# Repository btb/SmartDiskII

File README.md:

# SmartDiskII

The SmartDiskII is basically an Apple "Liron" disk controller with the IWM chip
replaced by the discrete components from the Disk II controller, which
the IWM was originally based on, and using firmware (i.e. SoftSP) which
has been appropriately modified to use those components instead of the IWM.

[Interactive BOM](https://btb.github.io/SmartDiskII/bom/SmartDiskII.html)

## SmartPort Operation

Because the SoftSP firmware (as of v6) is slot-dependent, a different copy is
required for each slot the card may be used in. The slot 1 version is in the 1xxx
region of the EPROM, slot 2 version is at 2xxx, etc.
A set of latches (U9) is used to automatically select the appropriate region
depending on which slot the SmartDiskII is placed in.

## Disk II Operation (experimental)

The card is designed to also work as a regular Disk II controller, though 
results can be inconsistent depending on the components used. Failures of 
this system can lead to corrupted floppy disks.

For this reason it is recommended to use true TTL ICs for all of the logic 
chips. In addition, for the chip at U5, Apple's original Disk II 
controller design called for a 9334 rather than a 74LS259. Indeed, using a 
9334 does appear to make the circuit more tolerant of these issues.  

5.25 Floppy operation works by having the Disk II boot rom in the 0xxx
region of the EPROM, and therefore active while U9 is held in
reset. Plugging a floppy drive into the DRV1 connector should automatically
activate the correct firmware because of the presence of +5V on pin 12, but
because some devices do not have that pin connected,
you can also close jumper JP8 to force the card into Disk II boot mode.

## Configuration

U8 is the standard [16-sector Disk II state machine data, P6](firmware/341-0128_P6A.bin), on a 2716-compatible EPROM.

U11 is a special combination of the Disk II boot ROM and the SoftSP firmware, [SmartDiskII.bin](firmware/SmartDiskII.bin).

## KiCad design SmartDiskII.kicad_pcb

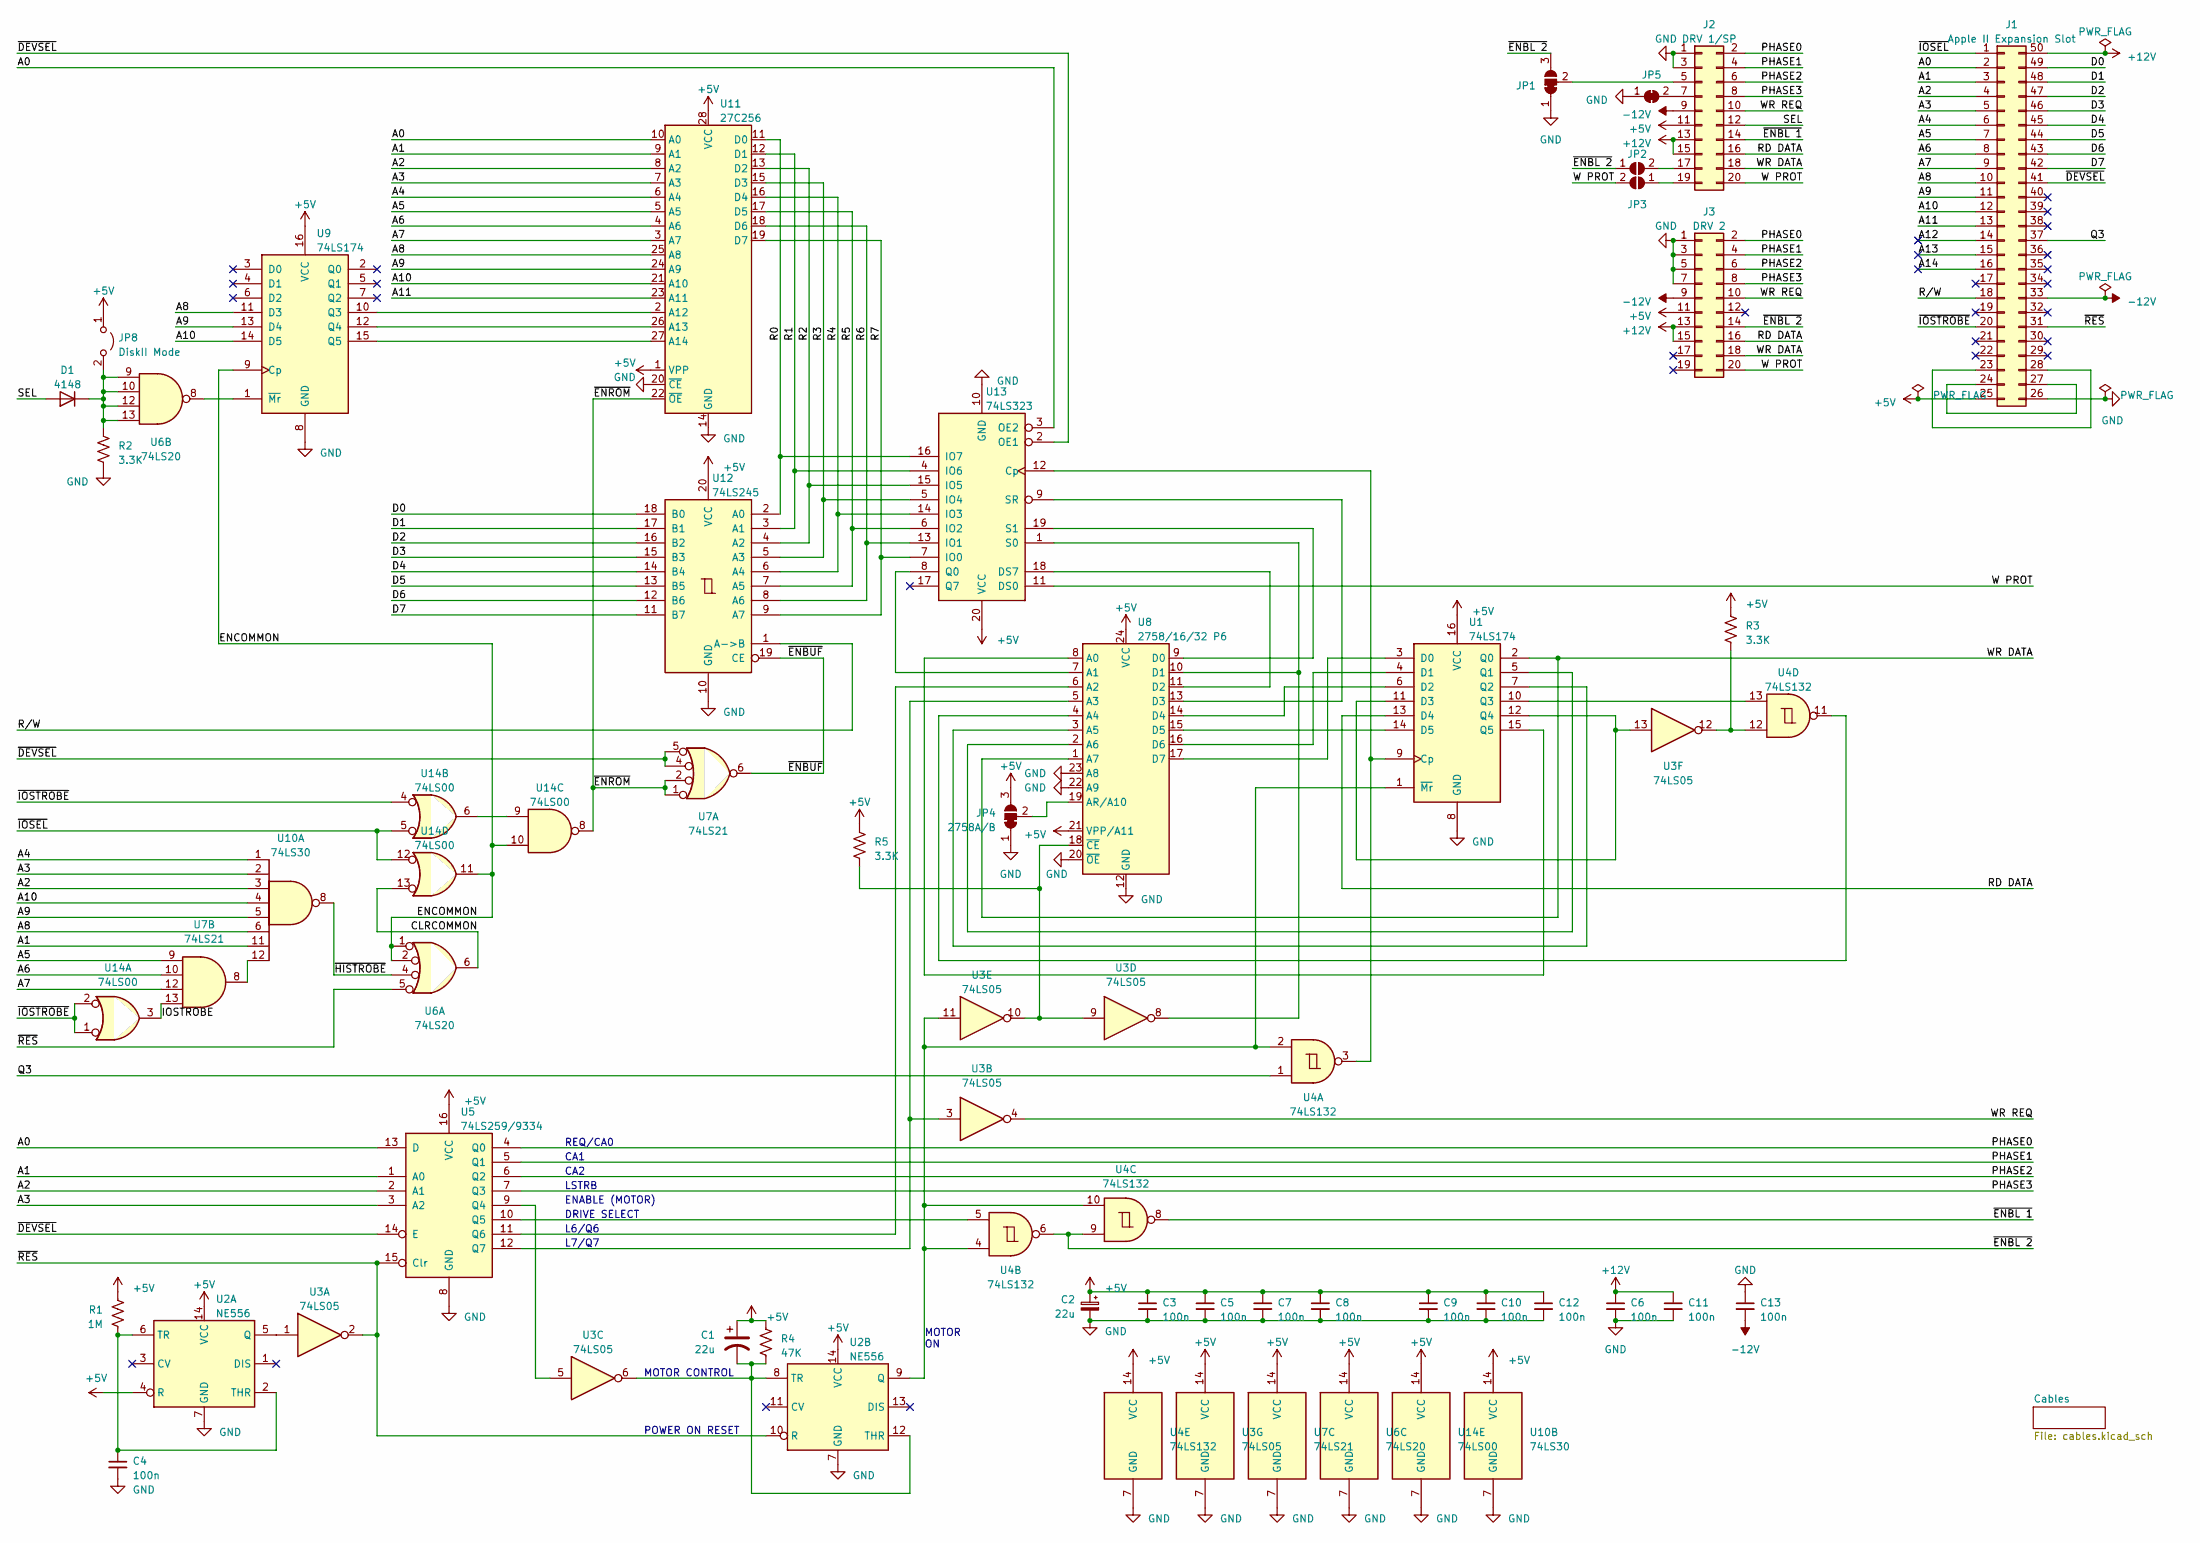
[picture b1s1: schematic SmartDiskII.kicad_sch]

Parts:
C1, C2: 22u; CP_Radial_D5.0mm_P2.50mm
C3, C4, C5, C6, C7, C8, C9, C10, C11, C12, C13: 100n; C_Disc_D4.3mm_W1.9mm_P5.00mm
D1: 4148; D_DO-35_SOD27_P7.62mm_Horizontal
J1: Apple II Expansion Slot; Apple II Expansion Edge Connector
J2: DRV 1/SP; PinHeader_2x10_P2.54mm_Vertical_Shrouded
J3: DRV 2; PinHeader_2x10_P2.54mm_Vertical_Shrouded
JP1: SolderJumper-3_P1.3mm_Bridged12_RoundedPad1.0x1.5mm_NumberL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
JP2, JP3: SolderJumper-2_P1.3mm_Open_RoundedPad1.0x1.5mm
JP4: 2758A/B; SolderJumper-3_P1.3mm_Bridged12_RoundedPad1.0x1.5mm_NumberL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
JP5: SolderJumper-2_P1.3mm_Bridged_RoundedPad1.0x1.5mm
JP8: DiskII Mode; PinHeader_1x02_P2.54mm_Vertical
R1: 1M; R_Axial_DIN0207_L6.3mm_D2.5mm_P10.16mm_Horizontal
R2, R3, R5: 3.3K; R_Axial_DIN0207_L6.3mm_D2.5mm_P10.16mm_Horizontal
R4: 47K; R_Axial_DIN0207_L6.3mm_D2.5mm_P10.16mm_Horizontal
U1, U9: 74LS174; DIP-16_W7.62mm
U2: NE556; DIP-14_W7.62mm
U3: 74LS05; DIP-14_W7.62mm
U4: 74LS132; DIP-14_W7.62mm
U5: 74LS259/9334; DIP-16_W7.62mm
U6: 74LS20; DIP-14_W7.62mm
U7: 74LS21; DIP-14_W7.62mm
U8: 2758/16/32 P6; DIP-24_W15.24mm
U10: 74LS30; DIP-14_W7.62mm
U11: 27C256; DIP-28_W15.24mm
U12: 74LS245; DIP-20_W7.62mm
U13: 74LS323; DIP-20_W7.62mm
U14: 74LS00; DIP-14_W7.62mm

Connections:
+5V: C1.1, C2.1, C3.1, C5.1, C7.1, C8.1, C9.1, C10.1, C12.1, J1.25, J2.11, J3.11, JP4.3 (B), JP8.1 (A), R1.1, R3.1, R4.2, R5.1, U1.16 (VCC), U2.4 (R), U2.14 (VCC), U3.14 (VCC), U4.14 (VCC), U5.16 (VCC), U6.14 (VCC), U7.14 (VCC), U8.21 (VPP/A11), U8.24 (VCC), U9.16 (VCC), U10.14 (VCC), U11.1 (VPP), U11.28 (VCC), U12.20 (VCC), U13.20 (VCC), U14.14 (VCC)
+12V: C6.1, C11.1, J1.50, J2.13, J2.15, J3.13, J3.15
-12V: C13.2, J1.33, J2.9, J3.9
/A0: J1.2, U5.13 (D), U11.10 (A0), U13.3 (OE2)
/A1: J1.3, U5.1 (A0), U10.11, U11.9 (A1)
/A2: J1.4, U5.2 (A1), U10.3, U11.8 (A2)
/A3: J1.5, U5.3 (A2), U10.2, U11.7 (A3)
/A4: J1.6, U10.1, U11.6 (A4)
/A5: J1.7, U7.9, U11.5 (A5)
/A6: J1.8, U7.10, U11.4 (A6)
/A7: J1.9, U7.12, U11.3 (A7)
/A8: J1.10, U9.11 (D3), U10.6, U11.25 (A8)
/A9: J1.11, U9.13 (D4), U10.5, U11.24 (A9)
/A10: J1.12, U9.14 (D5), U10.4, U11.21 (A10)
/A11: J1.13, U11.23 (A11)
/A12: J1.14
/A13: J1.15
/A14: J1.16
/CLRCOMMON: U6.6, U14.13
/D0: J1.49, U12.18 (B0)
/D1: J1.48, U12.17 (B1)
/D2: J1.47, U12.16 (B2)
/D3: J1.46, U12.15 (B3)
/D4: J1.45, U12.14 (B4)
/D5: J1.44, U12.13 (B5)
/D6: J1.43, U12.12 (B6)
/D7: J1.42, U12.11 (B7)
/ENCOMMON: U6.1, U6.2, U9.9 (Cp), U14.10, U14.11
/IOSTROBE: U7.13, U14.3
/PHASE0: J2.2, J3.2, U5.4 (Q0)
/PHASE1: J2.4, J3.4, U5.5 (Q1)
/PHASE2: J2.6, J3.6, U5.6 (Q2)
/PHASE3: J2.8, J3.8, U5.7 (Q3)
/Q3: J1.37, U4.1
/R0: U11.11 (D0), U12.2 (A0), U13.16 (IO7)
/R1: U11.12 (D1), U12.3 (A1), U13.4 (IO6)
/R2: U11.13 (D2), U12.4 (A2), U13.15 (IO5)
/R3: U11.15 (D3), U12.5 (A3), U13.5 (IO4)
/R4: U11.16 (D4), U12.6 (A4), U13.14 (IO3)
/R5: U11.17 (D5), U12.7 (A5), U13.6 (IO2)
/R6: U11.18 (D6), U12.8 (A6), U13.13 (IO1)
/R7: U11.19 (D7), U12.9 (A7), U13.7 (IO0)
/RD DATA: J2.16, J3.16, U1.13 (D4)
/R/W: J1.18, U12.1 (A->B)
/SEL: D1.2 (A), J2.12
/W PROT: J2.20, J3.20, JP3.2 (B), U13.11 (DS0)
/WR DATA: J2.18, J3.18, U1.2 (Q0), U8.1 (A7)
/WR REQ: J2.10, J3.10, U3.4
/~DEVSEL: J1.41, U5.14 (E), U7.4, U7.5, U13.2 (OE1)
/~ENBL 1: J2.14, U4.8
/~ENBL 2: J3.14, JP1.3 (B), JP2.1 (A), U4.6, U4.9
/~ENBUF: U7.6, U12.19 (CE)
/~ENROM: U7.1, U7.2, U11.22 (~OE), U14.8
/~HISTROBE: U6.4, U10.8
/~IOSEL: J1.1, U14.5, U14.12
/~IOSTROBE: J1.20, U14.1, U14.2, U14.4
/~RES: J1.31, U2.10 (R), U3.2, U5.15 (Clr), U6.5
GND: C2.2, C3.2, C4.2, C5.2, C6.2, C7.2, C8.2, C9.2, C10.2, C11.2, C12.2, C13.1, J1.26, J2.1, J2.3, J3.1, J3.3, J3.5, J3.7, JP1.1 (A), JP4.1 (A), JP5.1 (A), R2.2, U1.8 (GND), U2.7 (GND), U3.7 (GND), U4.7 (GND), U5.8 (GND), U6.7 (GND), U7.7 (GND), U8.12 (GND), U8.20 (~OE), U8.22 (A9), U8.23 (A8), U9.8 (GND), U10.7 (GND), U11.14 (GND), U11.20 (~CE), U12.10 (GND), U13.10 (GND), U14.7 (GND)
unnamed: D1.1 (K), JP8.2 (B), R2.1, U6.9, U6.10, U6.12, U6.13
unnamed: J1.23, J1.28
unnamed: J1.24, J1.27
unnamed: J2.5, JP1.2 (C)
unnamed: J2.7, JP5.2 (B)
unnamed: J2.17, JP2.2 (B)
unnamed: J2.19, JP3.1 (A)
unnamed: JP4.2 (C), U8.19 (AR/A10)
unnamed: R3.2, U3.12, U4.12
unnamed: U1.9 (Cp), U4.3, U13.12 (Cp)
unnamed: U1.3 (D0), U8.17 (D7)
unnamed: U1.4 (D1), U8.16 (D6)
unnamed: U1.6 (D2), U8.14 (D4)
unnamed: U1.11 (D3), U1.12 (Q4), U3.13
unnamed: U1.14 (D5), U8.15 (D5)
unnamed: U1.5 (Q1), U8.2 (A6)
unnamed: U1.7 (Q2), U8.3 (A5)
unnamed: U1.10 (Q3), U4.13
unnamed: U1.15 (Q5), U8.8 (A0)
unnamed: U1.1 (~Mr), U2.9 (Q), U3.11, U4.2, U4.4, U4.10
unnamed: U2.5 (Q), U3.1
unnamed: C4.1, R1.2, U2.2 (THR), U2.6 (TR)
unnamed: C1.2, R4.1, U2.8 (TR), U2.12 (THR), U3.6
unnamed: U3.5, U5.9 (Q4)
unnamed: U4.5, U5.10 (Q5)
unnamed: U5.11 (Q6), U8.6 (A2)
unnamed: U3.3, U5.12 (Q7), U8.5 (A3)
unnamed: U4.11, U8.4 (A4)
unnamed: R5.2, U3.9, U3.10, U8.18 (~CE)
unnamed: U6.8, U9.1 (~Mr)
unnamed: U7.8, U10.12
unnamed: U9.10 (Q3), U11.2 (A12)
unnamed: U9.12 (Q4), U11.26 (A13)
unnamed: U9.15 (Q5), U11.27 (A14)
unnamed: U8.11 (D2), U13.18 (DS7)
unnamed: U8.7 (A1), U13.8 (Q0)
unnamed: U3.8, U8.10 (D1), U13.1 (S0)
unnamed: U8.9 (D0), U13.19 (S1)
unnamed: U8.13 (D3), U13.9 (SR)
unnamed: U14.6, U14.9

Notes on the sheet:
MOTOR ON
CA2
REQ/CA0
POWER ON RESET
ENABLE (MOTOR)
L7/Q7
DRIVE SELECT
MOTOR CONTROL
L6/Q6
CA1
LSTRB

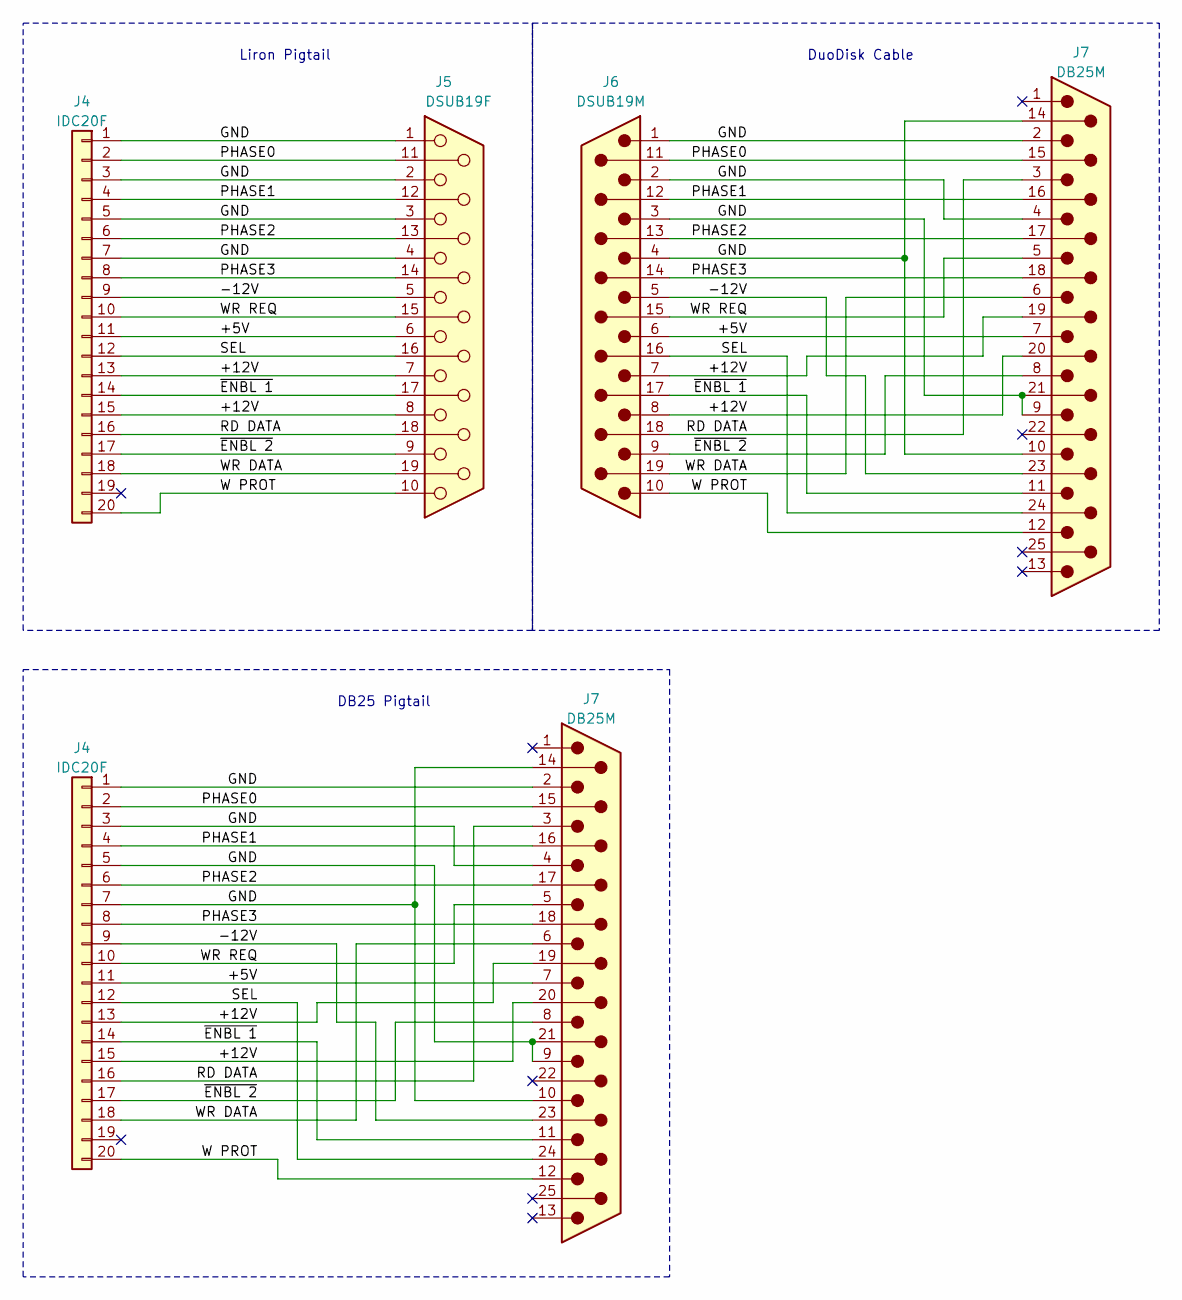
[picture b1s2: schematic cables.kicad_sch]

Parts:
J4: IDC20F
J5: DSUB19F
J6: DSUB19M
J7: DB25M

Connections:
unnamed: J4.1, J4.3, J4.5, J4.7, J5.1, J5.2, J5.3, J5.4, J6.1, J6.2, J6.3, J6.4, J7.2, J7.4, J7.9, J7.10, J7.14, J7.21
unnamed: J4.2, J5.11, J6.11, J7.15
unnamed: J4.4, J5.12, J6.12, J7.16
unnamed: J4.6, J5.13, J6.13, J7.17
unnamed: J4.8, J5.14, J6.14, J7.18
unnamed: J4.9, J5.5, J6.5, J7.23
unnamed: J4.10, J5.15, J6.15, J7.5
unnamed: J4.11, J5.6, J6.6, J7.7
unnamed: J4.12, J5.16, J6.16, J7.24
unnamed: J4.13, J4.15, J5.7, J5.8, J6.7, J6.8, J7.19, J7.20
unnamed: J4.14, J5.17, J6.17, J7.11
unnamed: J4.16, J5.18, J6.18, J7.3
unnamed: J4.17, J5.9, J6.9, J7.8
unnamed: J4.18, J5.19, J6.19, J7.6
unnamed: J4.20, J5.10, J6.10, J7.12

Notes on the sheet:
DuoDisk Cable
Liron Pigtail
DB25 Pigtail

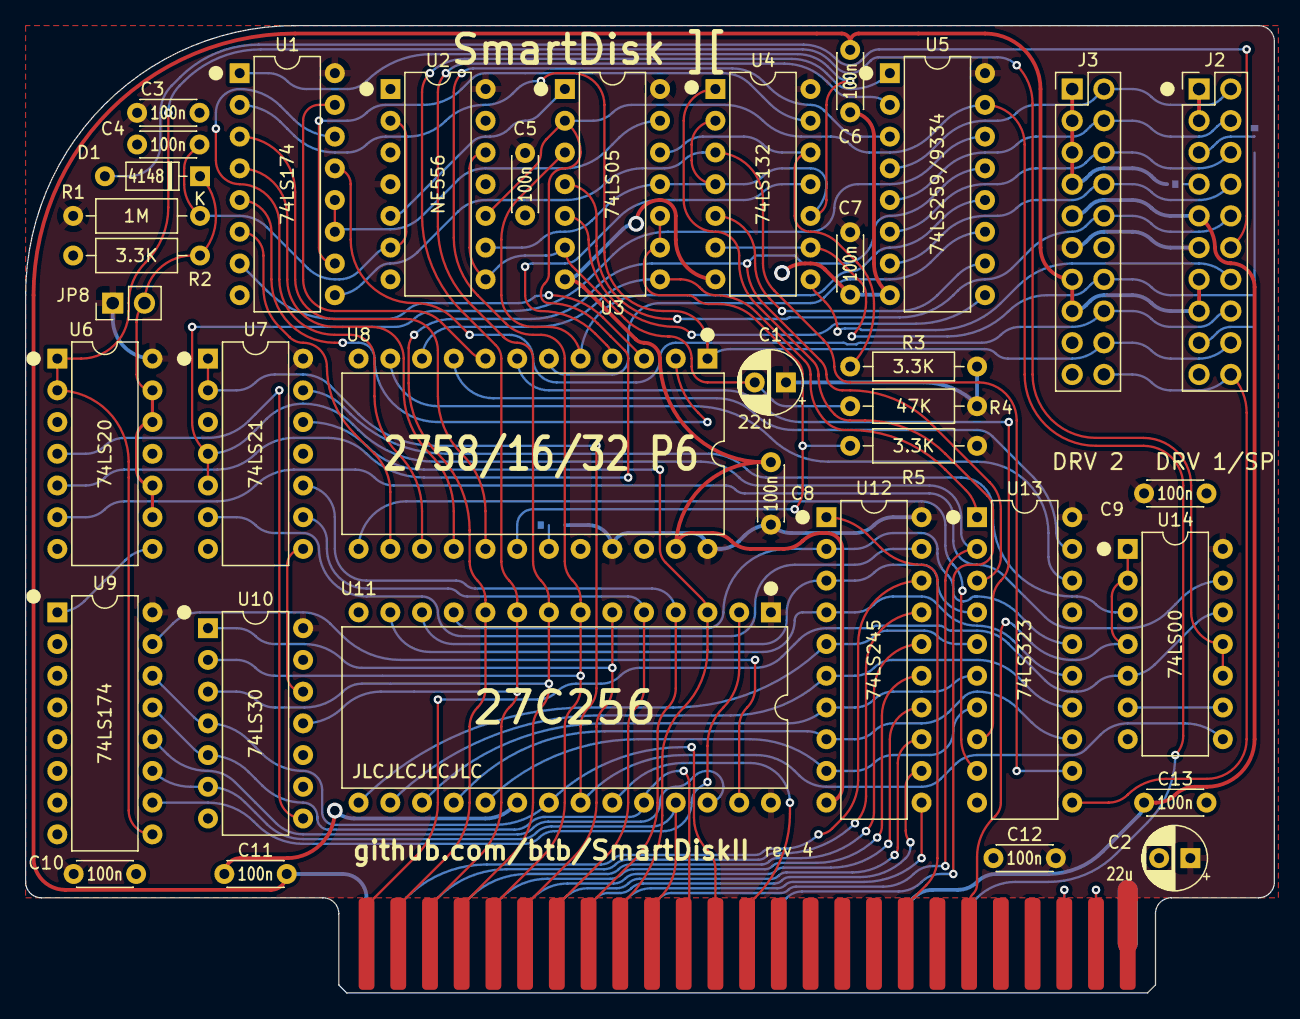
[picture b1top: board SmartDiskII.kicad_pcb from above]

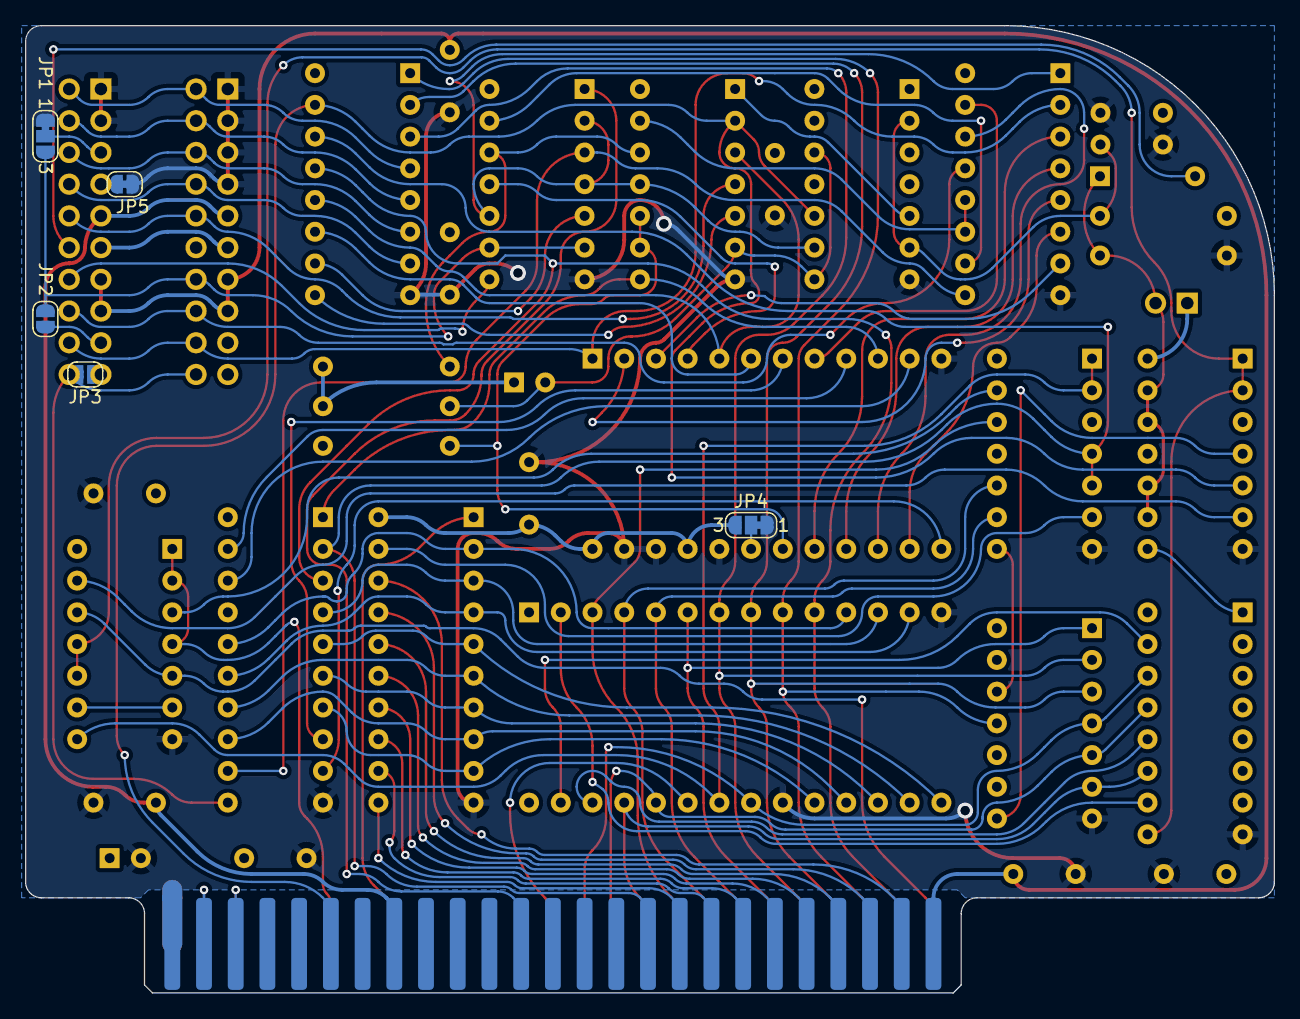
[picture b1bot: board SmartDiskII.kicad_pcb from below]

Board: 2 copper layers, 100.0 x 77.5 mm, 42 parts (5 on the bottom side), 95 nets.

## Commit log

2023-09-24 add board files
2023-09-24 add pages action
2023-09-24 new revision
    only one drive connector, configurable with jumpers
    optionally use 2764 EPROM
2023-09-24 update rev0 outputs
2023-09-24 rev2
2023-09-24 update kicad files
2023-09-24 use liron pinout with jumpers for EN2
2023-10-03 add page for cables
2023-10-03 update pdf
2023-10-09 All slot auto-switching rom
2023-10-11 fix jumper, tweaks
2023-10-12 Working circuit for multi-rom
2023-10-12 invert /SEL for auto detect of 5.25 floppy
2023-10-12 readd second floppy connector
    reference number changes
2023-10-12 add rev3 outputs
2023-10-20 Protect pin 12 with Diode
2023-10-22 add firmware
2023-10-22 Disk II firmware details
2023-10-22 tweaks
2023-10-22 Add P6 rom
2023-10-22 link to roms
2023-10-22 ignore
2023-10-22 whitespace
2023-10-29 use 3.3k instead of 3k. gnd jumper for drv pin 7
2023-10-29 remove old gerbers
2023-10-29 update docs
2024-01-11 ground drive pin 7 by default
2024-01-16 formatting
2024-01-27 housekeeping
2024-01-28 tweak back silkscreens
2024-01-28 rev4 final gerbers
